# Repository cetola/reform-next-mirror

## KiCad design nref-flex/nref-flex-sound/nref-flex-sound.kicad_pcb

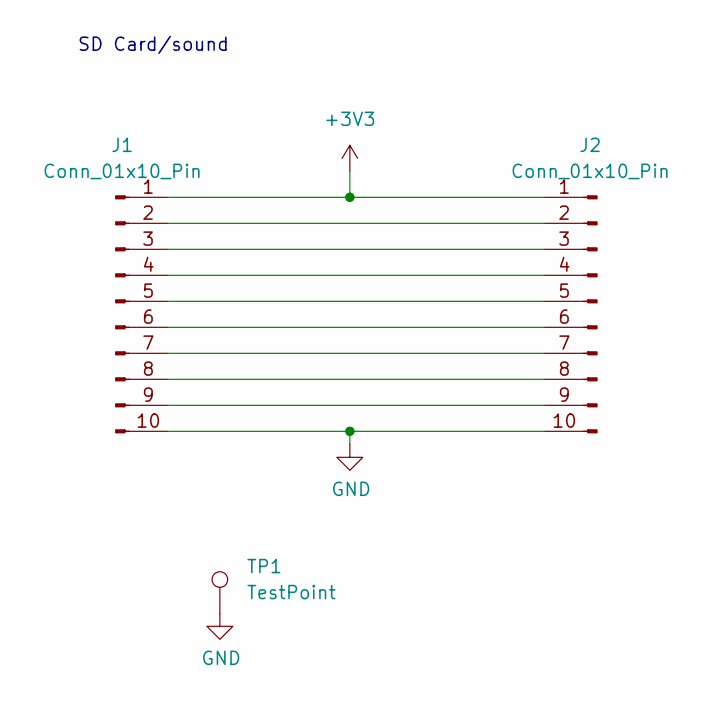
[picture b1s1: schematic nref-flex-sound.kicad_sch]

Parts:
J1, J2: Conn_01x10_Pin; FPC_10
TP1: TestPoint; TestPoint_Pad_D1.0mm

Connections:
+3V3: J1.1, J2.1
GND: J1.10, J2.10, TP1.1
unnamed: J1.2, J2.2
unnamed: J1.3, J2.3
unnamed: J1.4, J2.4
unnamed: J1.5, J2.5
unnamed: J1.6, J2.6
unnamed: J1.7, J2.7
unnamed: J1.8, J2.8
unnamed: J1.9, J2.9

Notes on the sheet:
SD Card/sound

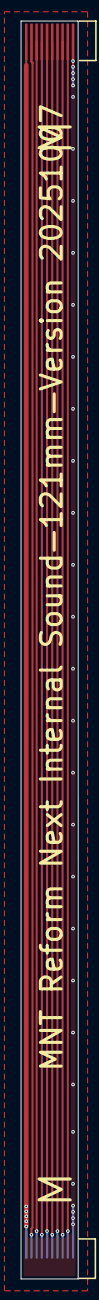
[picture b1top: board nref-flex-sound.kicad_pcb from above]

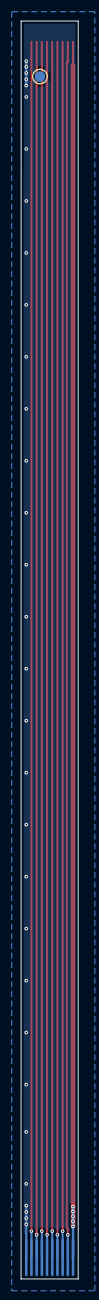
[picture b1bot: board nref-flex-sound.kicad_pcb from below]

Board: 2 copper layers, 5.5 x 121.0 mm, 3 parts (2 on the bottom side), 10 nets.

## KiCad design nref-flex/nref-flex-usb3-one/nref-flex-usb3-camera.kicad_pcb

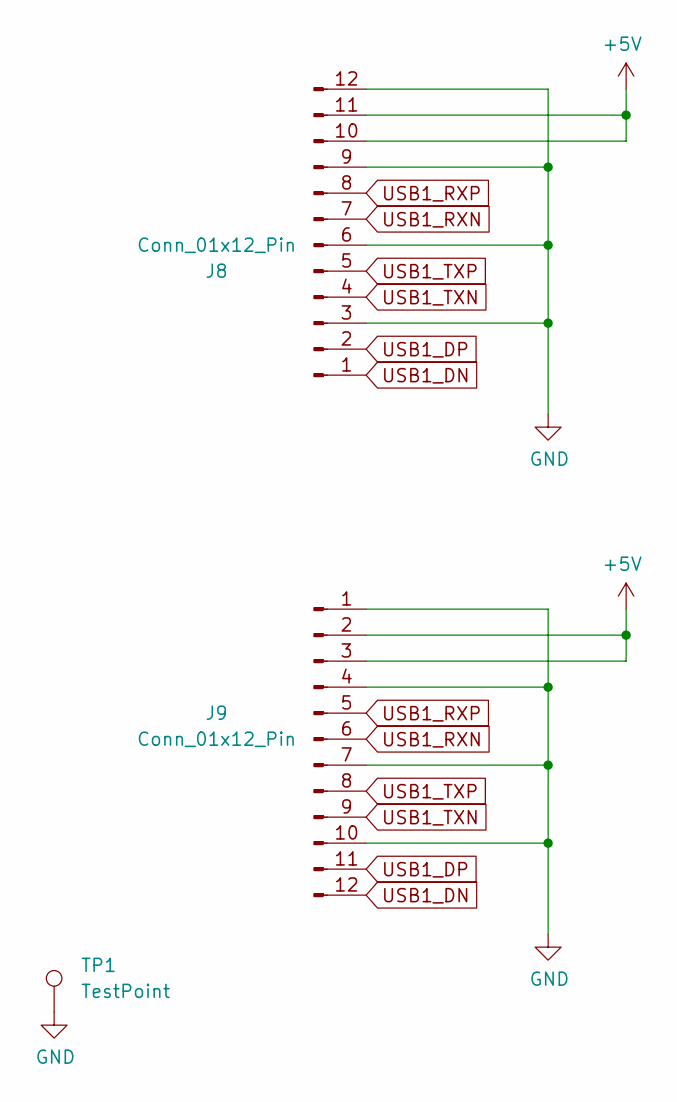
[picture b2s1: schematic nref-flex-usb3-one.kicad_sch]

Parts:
J8, J9: Conn_01x12_Pin; FPC_12
TP1: TestPoint; TestPoint_Pad_D1.0mm

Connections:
+5V: J8.10, J8.11, J9.2, J9.3
GND: J8.3, J8.6, J8.9, J8.12, J9.1, J9.4, J9.7, J9.10, TP1.1
USB1_DN: J8.1, J9.12
USB1_DP: J8.2, J9.11
USB1_RXN: J8.7, J9.6
USB1_RXP: J8.8, J9.5
USB1_TXN: J8.4, J9.9
USB1_TXP: J8.5, J9.8

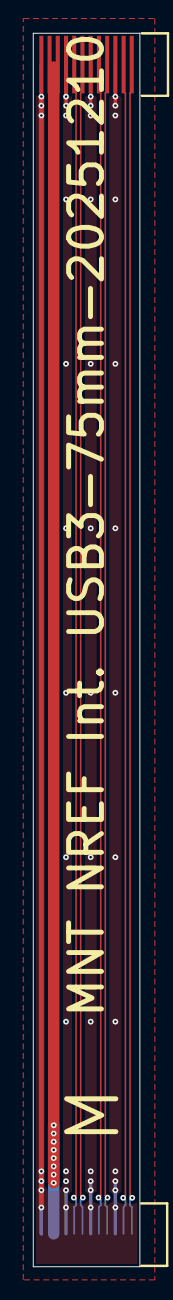
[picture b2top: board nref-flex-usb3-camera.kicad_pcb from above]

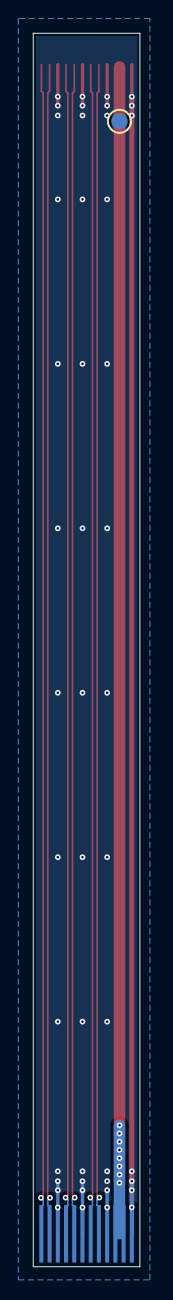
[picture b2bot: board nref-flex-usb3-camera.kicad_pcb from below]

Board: 2 copper layers, 6.5 x 75.0 mm, 3 parts (2 on the bottom side), 8 nets.

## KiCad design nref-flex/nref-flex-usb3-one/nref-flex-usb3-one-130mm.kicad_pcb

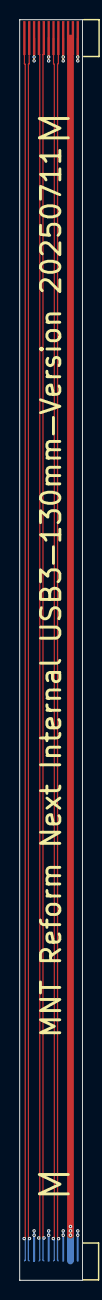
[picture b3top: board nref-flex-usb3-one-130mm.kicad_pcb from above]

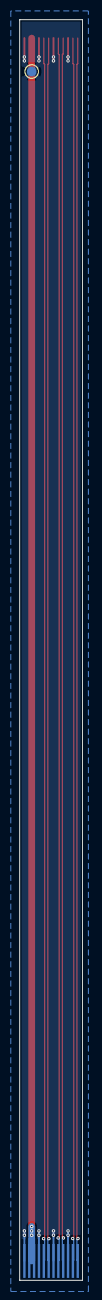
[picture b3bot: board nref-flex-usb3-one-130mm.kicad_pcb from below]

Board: 2 copper layers, 6.5 x 129.9 mm, 3 parts (2 on the bottom side), 8 nets.

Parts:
J8, J9: Conn_01x12_Pin; FPC_12
TP1: TestPoint; TestPoint_Pad_D1.0mm

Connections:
+5V: J8.2, J8.3, J9.10, J9.11
GND: J8.1, J8.4, J8.7, J8.10, J9.3, J9.6, J9.9, J9.12, TP1.1
USB1_DN: J8.12, J9.1
USB1_DP: J8.11, J9.2
USB1_RXN: J8.6, J9.7
USB1_RXP: J8.5, J9.8
USB1_TXN: J8.9, J9.4
USB1_TXP: J8.8, J9.5

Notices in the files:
nref-motherboard/nref-motherboard.kicad_sch:
MNT Research GmbH, Copyright 2026
License: CERN OHL-S 2.0
